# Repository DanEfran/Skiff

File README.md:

A small, never-finished Modular Synthesizer, emphasizing little 1u modules.

A "skiff" is a small-ish, often portable, modular synth rack -- compared to
the huge racks many folks covet. They are sometimes built into equipment
cases or the like, so they have latching lids and handles. Or a skiff might
just be a small-ish case, made of wood or whatever else suits the builder.

This skiff is presently a case made of foam core, though I consider that
a rough draft and expect to upgrade it to wood eventually. It has a pretty
standard DIY power supply (+12v/-12v) and a power distribution board with
some little connectors (not the big Eurorack standard ones, little servo-
style connectors with just the essential power lines) for the first batch
of modules. On the top edge are a power jack, power switch, and some MIDI
and audio jacks that aren't wired up yet. The rest is open space waiting
for small modules, which I'll build one at a time when I'm bored and have
free time between other projects. I expect this will take years and will
never be really finished, but hopefully the first few modules will make it
musically useful in some capacity.

The next step will be the output buffer/amplifier and a preliminary sound
source (possibly an arduino-powered module to jump-start the skiff).

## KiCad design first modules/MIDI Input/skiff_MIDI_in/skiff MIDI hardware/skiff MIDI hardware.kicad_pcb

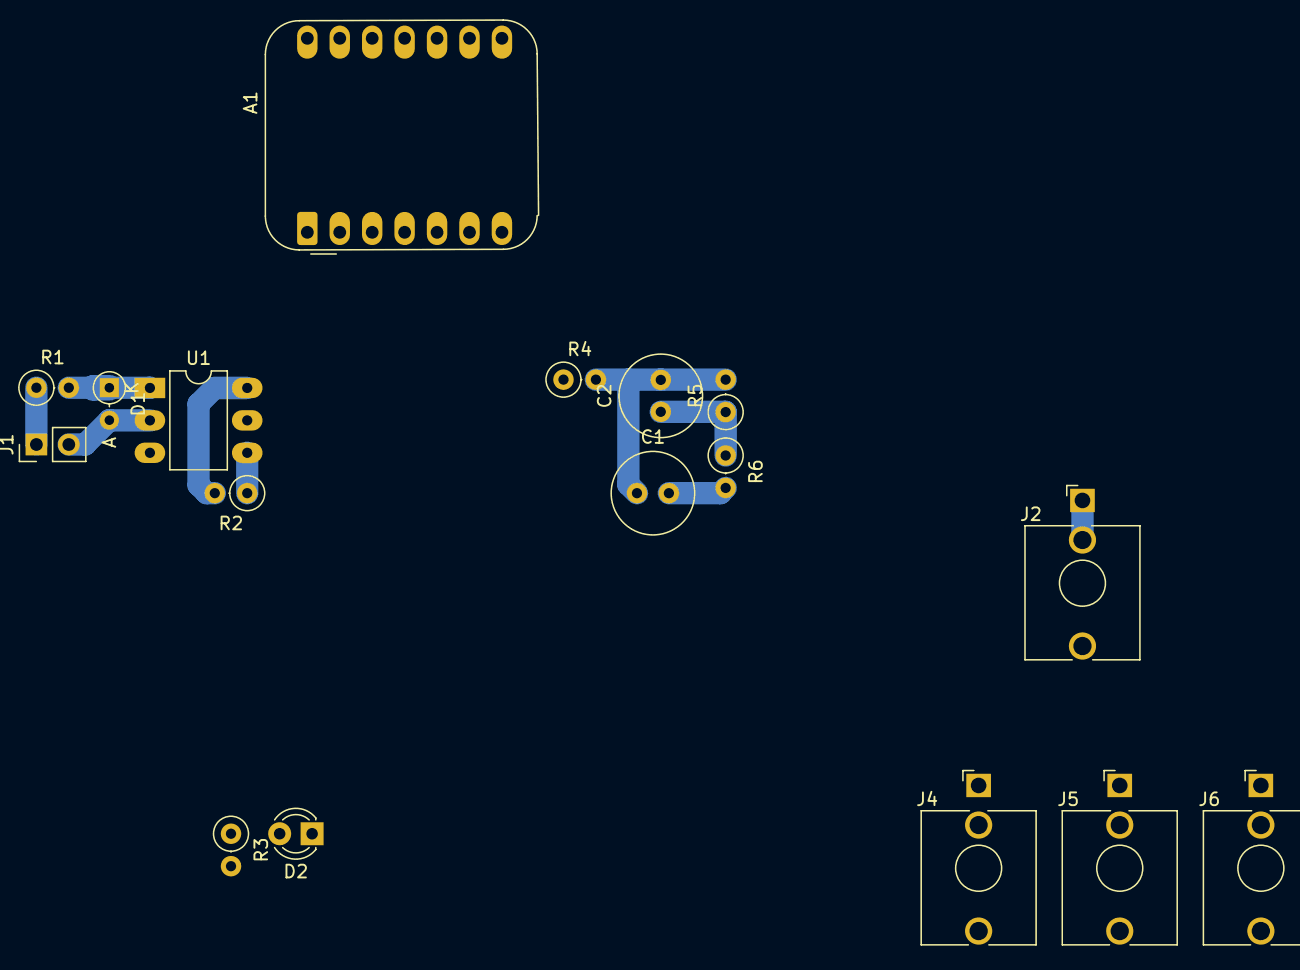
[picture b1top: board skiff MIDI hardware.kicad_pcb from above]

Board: 2 copper layers, 17 parts (0 on the bottom side), 12 nets.

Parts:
A1: Adafruit_QT_PY_RP2040_DSE
C1: 47u; C_Radial_D6.3mm_H7.0mm_P2.50mm
C2: 100n; C_Radial_D6.3mm_H7.0mm_P2.50mm
D1: D; D_DO-34_SOD68_P2.54mm_Vertical_AnodeUp
D2: LED; LED_D3.0mm
J1: PinHeader_1x02_P2.54mm_Vertical
J2: Audio Out; Jack_3.5mm_QingPu_WQP-PJ398SM_Vertical_CircularHoles
J4: CV Out; Jack_3.5mm_QingPu_WQP-PJ398SM_Vertical_CircularHoles
J5: Gate Out; Jack_3.5mm_QingPu_WQP-PJ398SM_Vertical_CircularHoles
J6: Clock Out; Jack_3.5mm_QingPu_WQP-PJ398SM_Vertical_CircularHoles
R1, R4: 220; R_Axial_DIN0207_L6.3mm_D2.5mm_P2.54mm_Vertical
R2: 470; R_Axial_DIN0207_L6.3mm_D2.5mm_P2.54mm_Vertical
R3: 2k2; R_Axial_DIN0207_L6.3mm_D2.5mm_P2.54mm_Vertical
R5: 100; R_Axial_DIN0207_L6.3mm_D2.5mm_P2.54mm_Vertical
R6: 1k8; R_Axial_DIN0207_L6.3mm_D2.5mm_P2.54mm_Vertical
U1: H11L1; DIP-6_W7.62mm_LongPads

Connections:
+3V3: A1.12 (3V3), R2.2, R3.2, U1.6
A0: A1.1 (A0), D2.1 (K), R2.1, U1.4
GND: A1.13 (GND), C2.1, J2.R, J2.S, R5.1, R6.1, U1.5
unnamed: A1.2 (A1), J6.T
unnamed: A1.8 (RX), J5.T
unnamed: C1.1, C2.2, R4.2, R5.2
unnamed: C1.2, J2.T, R6.2
unnamed: D1.2 (A), J1.2, U1.2
unnamed: D1.1 (K), R1.2, U1.1
unnamed: D2.2 (A), R3.1
unnamed: J1.1, R1.1
TX: A1.7 (TX), R4.1

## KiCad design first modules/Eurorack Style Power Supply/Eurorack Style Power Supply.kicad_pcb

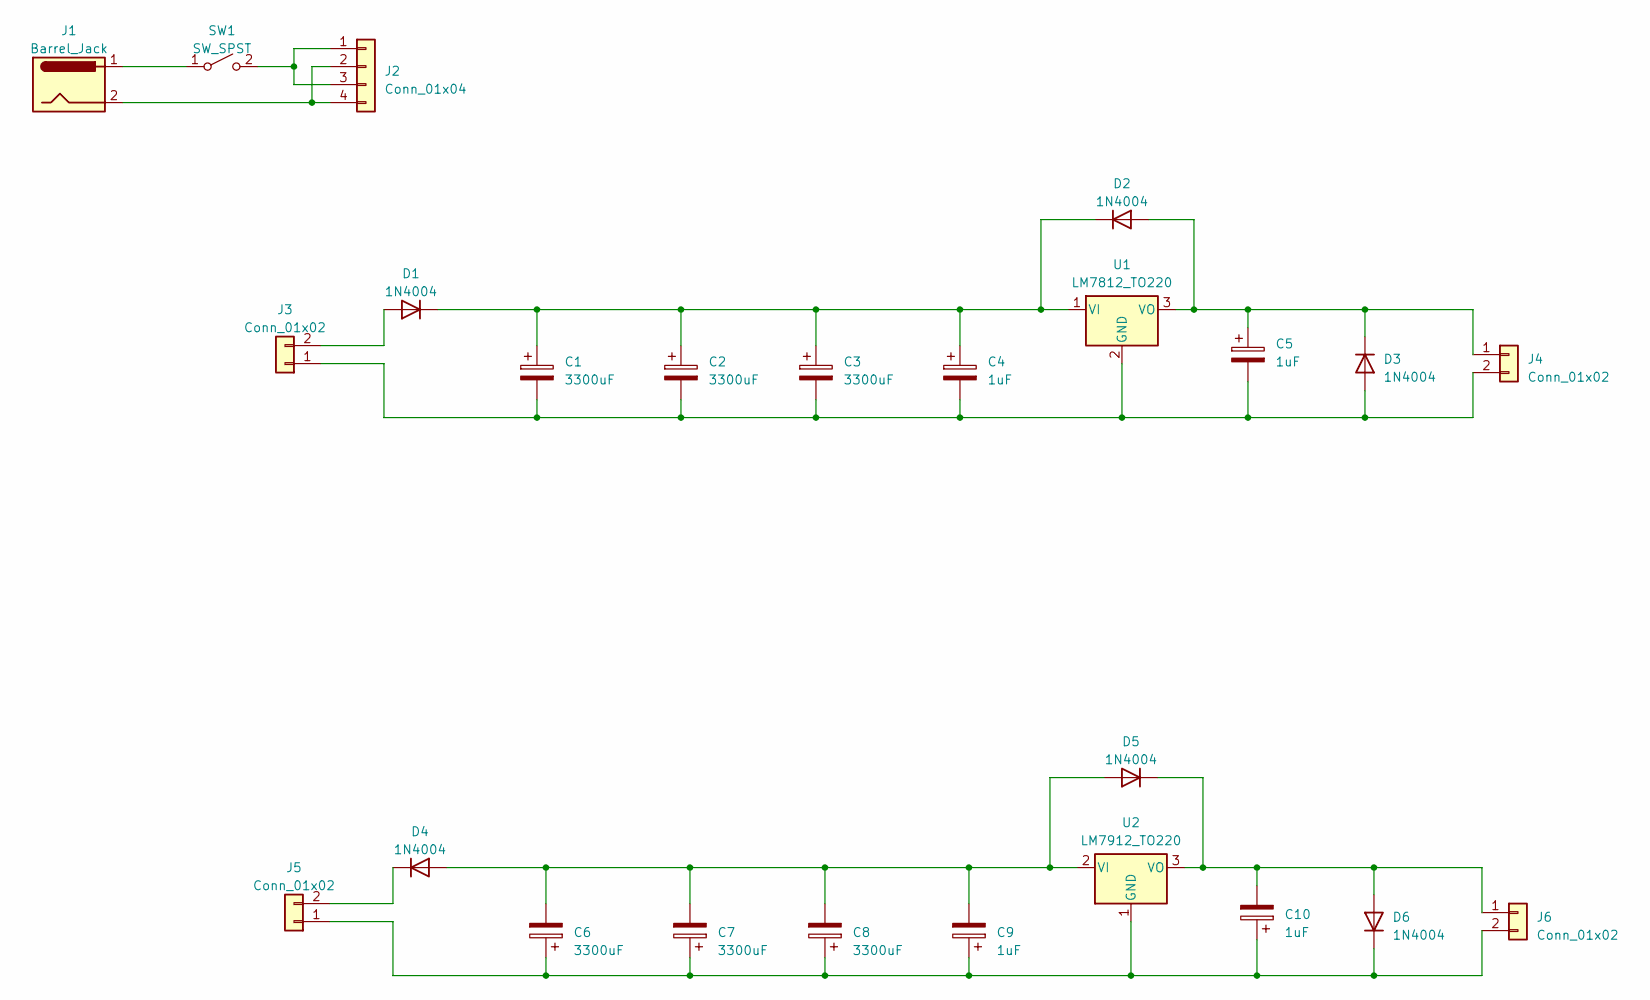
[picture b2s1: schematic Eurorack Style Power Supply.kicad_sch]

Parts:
C1, C2, C3, C6, C7, C8: 3300uF; CP_Axial_L30.0mm_D18.0mm_P35.00mm_Horizontal
C4, C5, C9, C10: 1uF; CP_Radial_Tantal_D4.5mm_P2.50mm
D1, D2, D3, D4, D5, D6: 1N4004; D_DO-41_SOD81_P10.16mm_Horizontal
J1: Barrel_Jack; BarrelJack_CUI_PJ-063AH_Horizontal_CircularHoles
J2: Conn_01x04; PinHeader_1x04_P2.54mm_Vertical
J3, J4, J5, J6: Conn_01x02; PinHeader_1x02_P2.54mm_Vertical
SW1: SW_SPST; SW_Lever_1P2T_NKK_GW12LxH
U1: LM7812_TO220; TO-220-3_Vertical
U2: LM7912_TO220; TO-220-3_Vertical

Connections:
unnamed: D1.2 (A), J3.2
unnamed: C1.1, C2.1, C3.1, C4.1, D1.1 (K), D2.1 (K), U1.1 (VI)
unnamed: C5.1, D2.2 (A), D3.1 (K), J4.1, U1.3 (VO)
unnamed: C1.2, C2.2, C3.2, C4.2, C5.2, D3.2 (A), J3.1, J4.2, U1.2 (GND)
unnamed: C6.2, C7.2, C8.2, C9.2, D4.2 (A), D5.2 (A), U2.2 (VI)
unnamed: D4.1 (K), J5.2
unnamed: C10.2, D5.1 (K), D6.2 (A), J6.1, U2.3 (VO)
unnamed: C6.1, C7.1, C8.1, C9.1, C10.1, D6.1 (K), J5.1, J6.2, U2.1 (GND)
unnamed: J2.1, J2.3, SW1.2 (B)
unnamed: J1.2, J2.2, J2.4
unnamed: J1.1, SW1.1 (A)

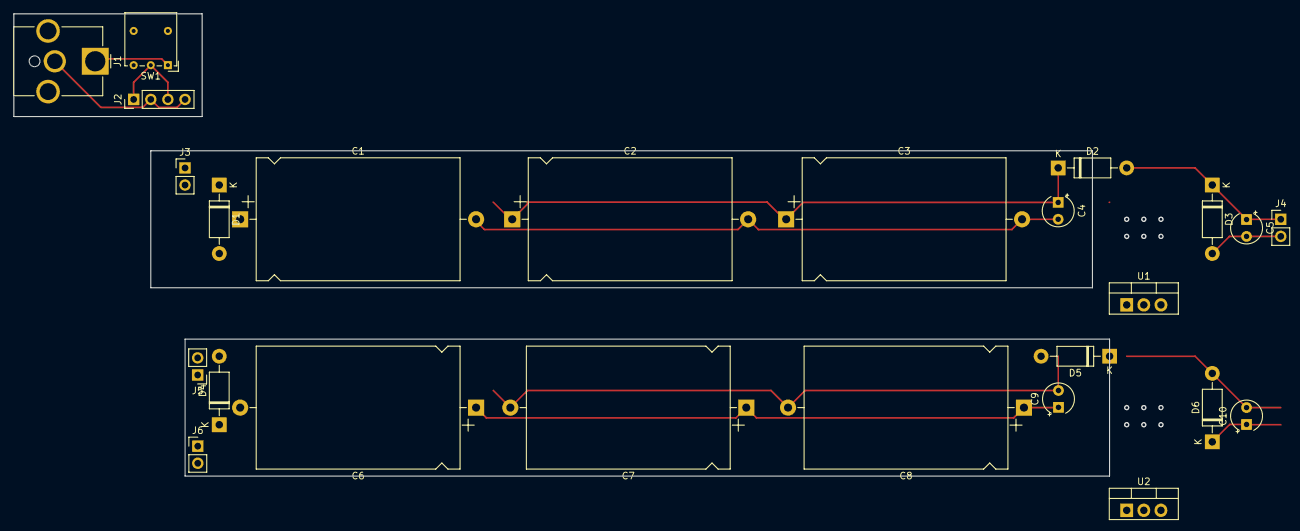
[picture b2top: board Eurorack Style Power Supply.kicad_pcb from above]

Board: 2 copper layers, 162.6 x 68.6 mm, 25 parts (0 on the bottom side), 11 nets.

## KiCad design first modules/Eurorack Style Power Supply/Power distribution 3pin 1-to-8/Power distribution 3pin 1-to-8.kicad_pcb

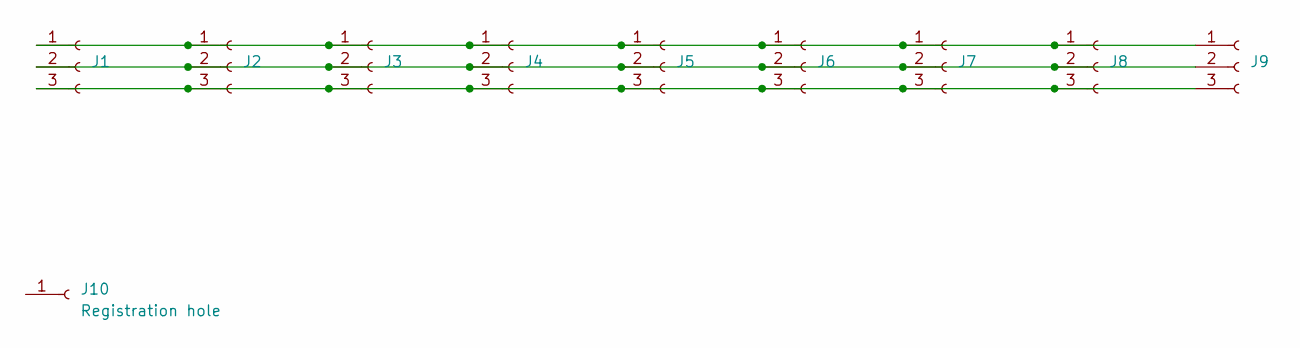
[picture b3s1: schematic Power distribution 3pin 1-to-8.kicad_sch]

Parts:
J1, J2, J3, J4, J5, J6, J7, J8, J9: Conn_01x03_Socket; PinHeader_1x03_P2.54mm_Vertical
J10: Registration hole; PinHeader_1x01_P2.54mm_Vertical

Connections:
unnamed: J1.1, J2.1, J3.1, J4.1, J5.1, J6.1, J7.1, J8.1, J9.1
unnamed: J1.2, J2.2, J3.2, J4.2, J5.2, J6.2, J7.2, J8.2, J9.2
unnamed: J1.3, J2.3, J3.3, J4.3, J5.3, J6.3, J7.3, J8.3, J9.3
registration: J10.1

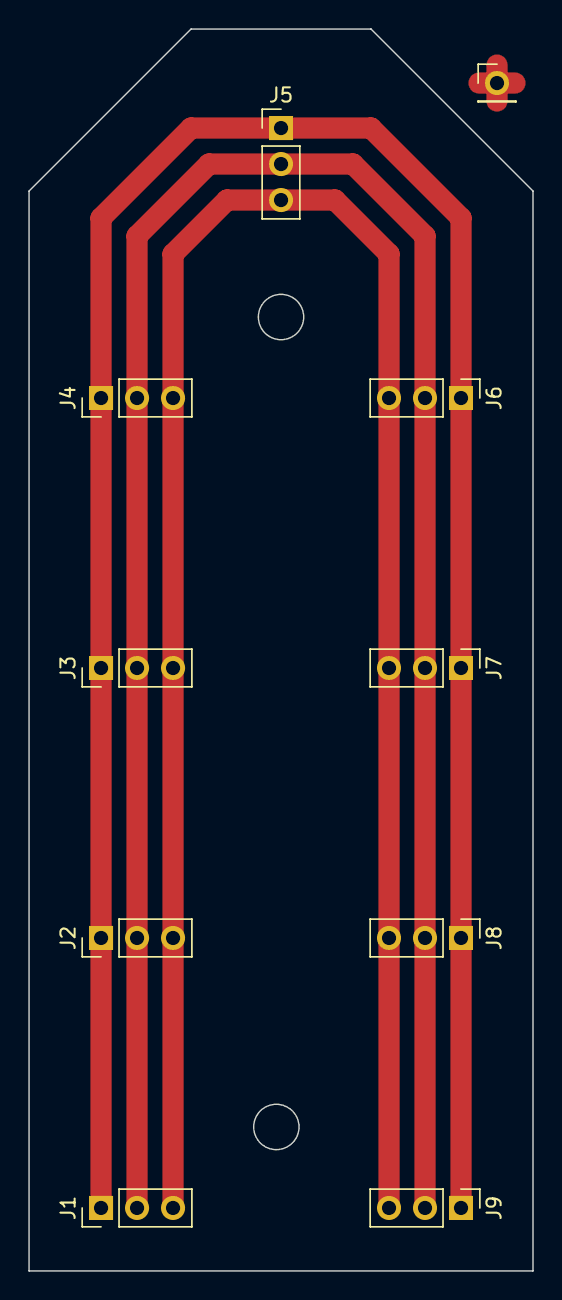
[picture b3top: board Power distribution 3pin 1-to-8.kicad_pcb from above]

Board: 2 copper layers, 35.6 x 87.6 mm, 10 parts (0 on the bottom side), 3 nets.

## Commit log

2024-12-20 Initial git commit of progress so far: Power Supply board is done; Power distribution board is done; the foam-core first draft skiff case is done; the top panel with power switch etc. is done, at lea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
2024-12-20 Add .gitignore
2025-02-11 More notes on this project.
2025-02-11 MIDI In: schematic & PCB: several subsections
2025-02-11 PCB in progress; Schematic lacks only output stages (Outputs don't yet conform to Modular Synth signal standards, but schematic should be otherwise ok.)
2025-02-11 .gitignore: more
2025-02-11 Main arduino sketch file: just example code so far (checking that the display works; MIDI test is in a separate sketch, soon to be added to this one)
2025-02-11 Minor changes to files. New KiCad version
2025-02-11 Sch: Add Rotary Encoder; move DAC to Stemma QT i2c; Remove Clock output (it was an optional bonus, but there's no pin available for it. I suppose we could chain additional outputs onto the Stemma QT 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
2025-02-20 NOTES: more
2025-03-01 Schematic: add power switch. minor cleanup.
2025-03-01 Moved display example code into display.cpp/.h
2025-03-02 dead code cleanup
2025-03-02 Add onboard neopixel blink in neopixel.cpp/.h Sanity check: loop is running. (This fairly simple sketch will begin as a collection of example code, proving the hardware subsystems work, then evolve.)
2025-03-02 Add SimpleSynth example code in its own file(s). MILESTONE: MIDI input produces basic Audio and Gate outputs, and display is working (though not showing anything of interest yet). CV output is not ye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
2025-03-03 Rotary encoder: simple test in rotary.cpp/.h
2025-03-03 Rotary encoder: monitored via interrupts. Proof-of-concept only: Serial printing inside the interrupt handlers; knob badly needs debouncing. So these are not the real interrupt handlers, but the wiri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
2025-03-03 Notes: status: DAC isn't working. need a new one?
2025-03-03 Notes: status: DAC isn't working. need a new one? Hardware lacks output buffers, but not much else!
2025-03-03 New DAC board: simple test in DAC.cpp/.h; it works. Voltage in early tests doesn't seem to match the nominal/expected reference; test more. But any consistent voltage will work. Now this module just 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
